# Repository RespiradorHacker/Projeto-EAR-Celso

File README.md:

# e-AR (EAR) PROJECT - EMERGENCY VENTILATOR
This project was born because of CoVid19 pandemic.
The project Goal is to provide an emergency ventilator system to help CoVid19 serious cases using locally available resources. eAR was designed to meet specifications according to MHRA (UK) - Rapidly Manufactured Ventilator System and inspired by MIT E-Vent (USA) concepts and specs.

This is an OPEN HARDWARE - OPEN SOURCE PROJECT. 

DISCLAIMER: we will NOT take any responsability on devices built using partial or total information from this project. 
Any device used for life support and medical applications must meet all local requirements and they must be homologated by local regulatory agencies in ANY case.

The target is to run an entire ventilation system using an automotive car battery and an O2 can.
The initial project leader is Celso Ken Mori Monteiro, automotive designer with +30 yrs experience on automotive embedded systems
as OEM designer for customers as GM, Ford, VW, Fiat, Mercedes Benz, Scania, Navistar, Marcopolo, Agco...

The technology for first PCBs was downsized due to components availability in emerging countries so distributed production could be achieved even in small brazilian towns. The electronic parts are:
- PTH components
- Single-sided PCB, obtainable even by DIYs. 

Besides inclusive concept there is also a FR4 SMT version available for volume production.

Basic concepts:
- External FIO2 O2 + AIR mixer based on timed mechanical truck air valves and plastic bag container
- AMBU smasher based on car window motor due to availabilty and great mechanical characteristics. Motor reversion is necessary to allow dinamic changes of BPM, Tidal Volume, pressure ramping, I/E Ratio and Plateau Hold Time without ANY mechanical change.
- ECU based on Arduino Pro Mini (the most available in emerging countries) and SPI based IO expension
- 2 motor drive options: relay (need second adjustable supply or buck) and PWM driven mosfet driver

Project Evolution:
- full HW schematics and system component's description available on "EAR System Developer's HW Guide", portuguese only version
- PCB Gerbers available, Single Side PTH version, Motor driver on relay option only. Time and size were underestimated because we no longer use these old technologies. Released on March 30, 2020.
- Mech prototype phase 2 aproved, torque is OK and current is low.
- Gerbers of single sided boards on PTH components published on March 30, 2020. Time and size were underestimated because we no longer use these old technologies. 
- EAR System Developer's SW Guide released on March 30, 2020.
- Functional electronics prototype built and delivered on April 2, 2020. No changes in PCBs are necessary except hardware end-of-courses provided for EAR ECU Motor Driver Board. Test driven by firmware FW00 - focused on HW testing only. Reads input pots, control motor with reversal action, measures motor current and tests IO expansion board. All items are functional.
- FW00 published in April 3, 2020.
- Added Mosfet-based PWM Motor Driver and Absolute position sensor using a car fuel level sensor.
- First working mechanical+electrical prototype delivered in April 6, 2020.
- Added Pressure Sensor in April 7, 2020. First artificial lung is a balloon so first pressure profile was obtained. It Sounds promising.
- Firmware controls Tidal Volume and BPM according to Set Potentiometers. First functional firmware produce variable pressure ramps as needed, FW met 8-30 BPM dynamic range specification.
- Added motor cutoff in inspiratory phase according to pressure preset on pot Overpressure Threshold within 1cm H20 resolution.
- Added full mechanical design for functional AMBU compressing ARM in April 11, 2020
- Added in April 12, 2020: Motor Driver, mosfet NN version. Full Kicad design with schematics, PCB and Gerbers.
- Added in April 12,2020: eAR External watchdog Timer to increase eAR reliability. Full Eagle design with schematics, PCB and Gerbers.
- Added in April 13,2020: I/E selection (1:1, 1:2, 1:3 and 1:4) and Plateau Hold Time selection (150, 250, 500 and 1000ms hold on Plateau)
- Added in April 13,2020: Gol G3 tank level float sensor added as absolute position sensor. Increased linearity, resolution and availability
- Mech proto 3.2 added ball bearing in compression arm, currently performing cycling tests
- Added in April 15,2020; eAR Pressure sensor Board Design and PCB, MPX5010DP supported
- Added in April 21,2020: 10x10cm FR4 SMT single PCB design for volume production, verified design, send to production
- Added in April 21,2020: Mechanical proto 3.2 drawings delivered, functional design
- April 30, 2004: eAR FR4 Single-Board PCBs arrived, courtesy from Digicart/SC
- May 1st, 2020: eAR system reached 14 days of 24/7 operation, with 403,412 beathing cycles completed. eAR met minimum durability MHRA (UK) Spec with a prototype built on MDF, a window lift BDC motor and a 20-yrs-old chevy tank float sensor
- May 5, 2020: Multiple pressure sensor added, allowing almost any kind of linear pressure sensor to be connected to eAR system, including MPX5010, MPX10 almost all versions and packages including MPVZ and MP3V and experimental ultra-low-cost MPS20N0040D-S sensor
- May 12, 2020: Integrated EAR ECU tested, functional test OK. Some minor drilling errors corrected, some improvements done and new PCB generated. New mosfet driver option added in firmware as needed. Some components changed values due to standardization effort to ease production. eAR electronics is ready for mass production.
- May 23, 2020: Added first steel based eAR mechanical design, by Ricardo Suzuki. Arm sensor changed to DS 1901 non-contact TPS. 
- June 1st, 2020: Added R2 of mechanical design in two verions, geared arm and 4-linked-bars by Ricardo Suzuki

Pending:
- Software reliability improvements.
- Assisted Ventilation Firmware on hold. It can delay ANVISA aproval when requested.

Special thanks to all people that made this project real!
It's impossible to list all names involved, I apologize for forgetting someone.
The partial list follows:

Project Contributors, as they have joined this project
- Joannes Berque (FR): first design idea.
- Celso Monteiro: eletronics and firmware design, system conception and documentation.
- Diego Padilha and Lucas Pianizzer: electronics and mechanical design+prototyping. 
- Marcelo Pires: electronic CAD, schematics capture & PCB Design.
- Nicolai Rutkevich: mechanical concepts.
- Bruno Afogliatto: decontamination concepts.
- Gustavo Ortenzi: motor drive alteratives.
- Ricardo Suzuki: system concepts and mechanical design.
- Rodrigo Azevedo: organized Github Project.
- Douglas Esteves: interface with other projects.
- João Cardoso and Leonardo Afonso: Kicad Capture for Open Hardware.
- Andre Novelli e Victor Acioly: AMBU bags replacement.
- Flavio Alves: GUI design
- David Loos: electronics assembly

References:
- MIT E-Vent: human requirements and system conception ideas.
- MHRA (UK) Rapidly Manufactured Ventilator System

Healthcare professionals involved:
- Angelica Mammana M.D. helped stablishing specs and performed crytical analysis.
- Fernando Machado M.D. was the first contributing doctor.
- Lucio Flavio M.D.
- Ana Teresa Gama.

Project supporters:
- Fabio Knihs.
- Norberto Tomio.
- Gabriel Casagrande.
- Ivandro Ceccato.

Thanks to my family, special thanks to my dear wife Tissa and my children Joana, Gustavo and Leonardo, for their unlimited support and to all the people that prayed for this project, and God that inspired and guided me all the time.

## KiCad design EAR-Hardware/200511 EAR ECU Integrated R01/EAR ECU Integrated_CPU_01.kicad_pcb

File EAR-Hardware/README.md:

# EAR ECU
Projeto iniciado por Celso Monteiro

- released RDSV200329 EAR System Developer's HW Guide PTBR R00
- This document has details on EAR ECU hardware and its components
- OPEN HARDWARE

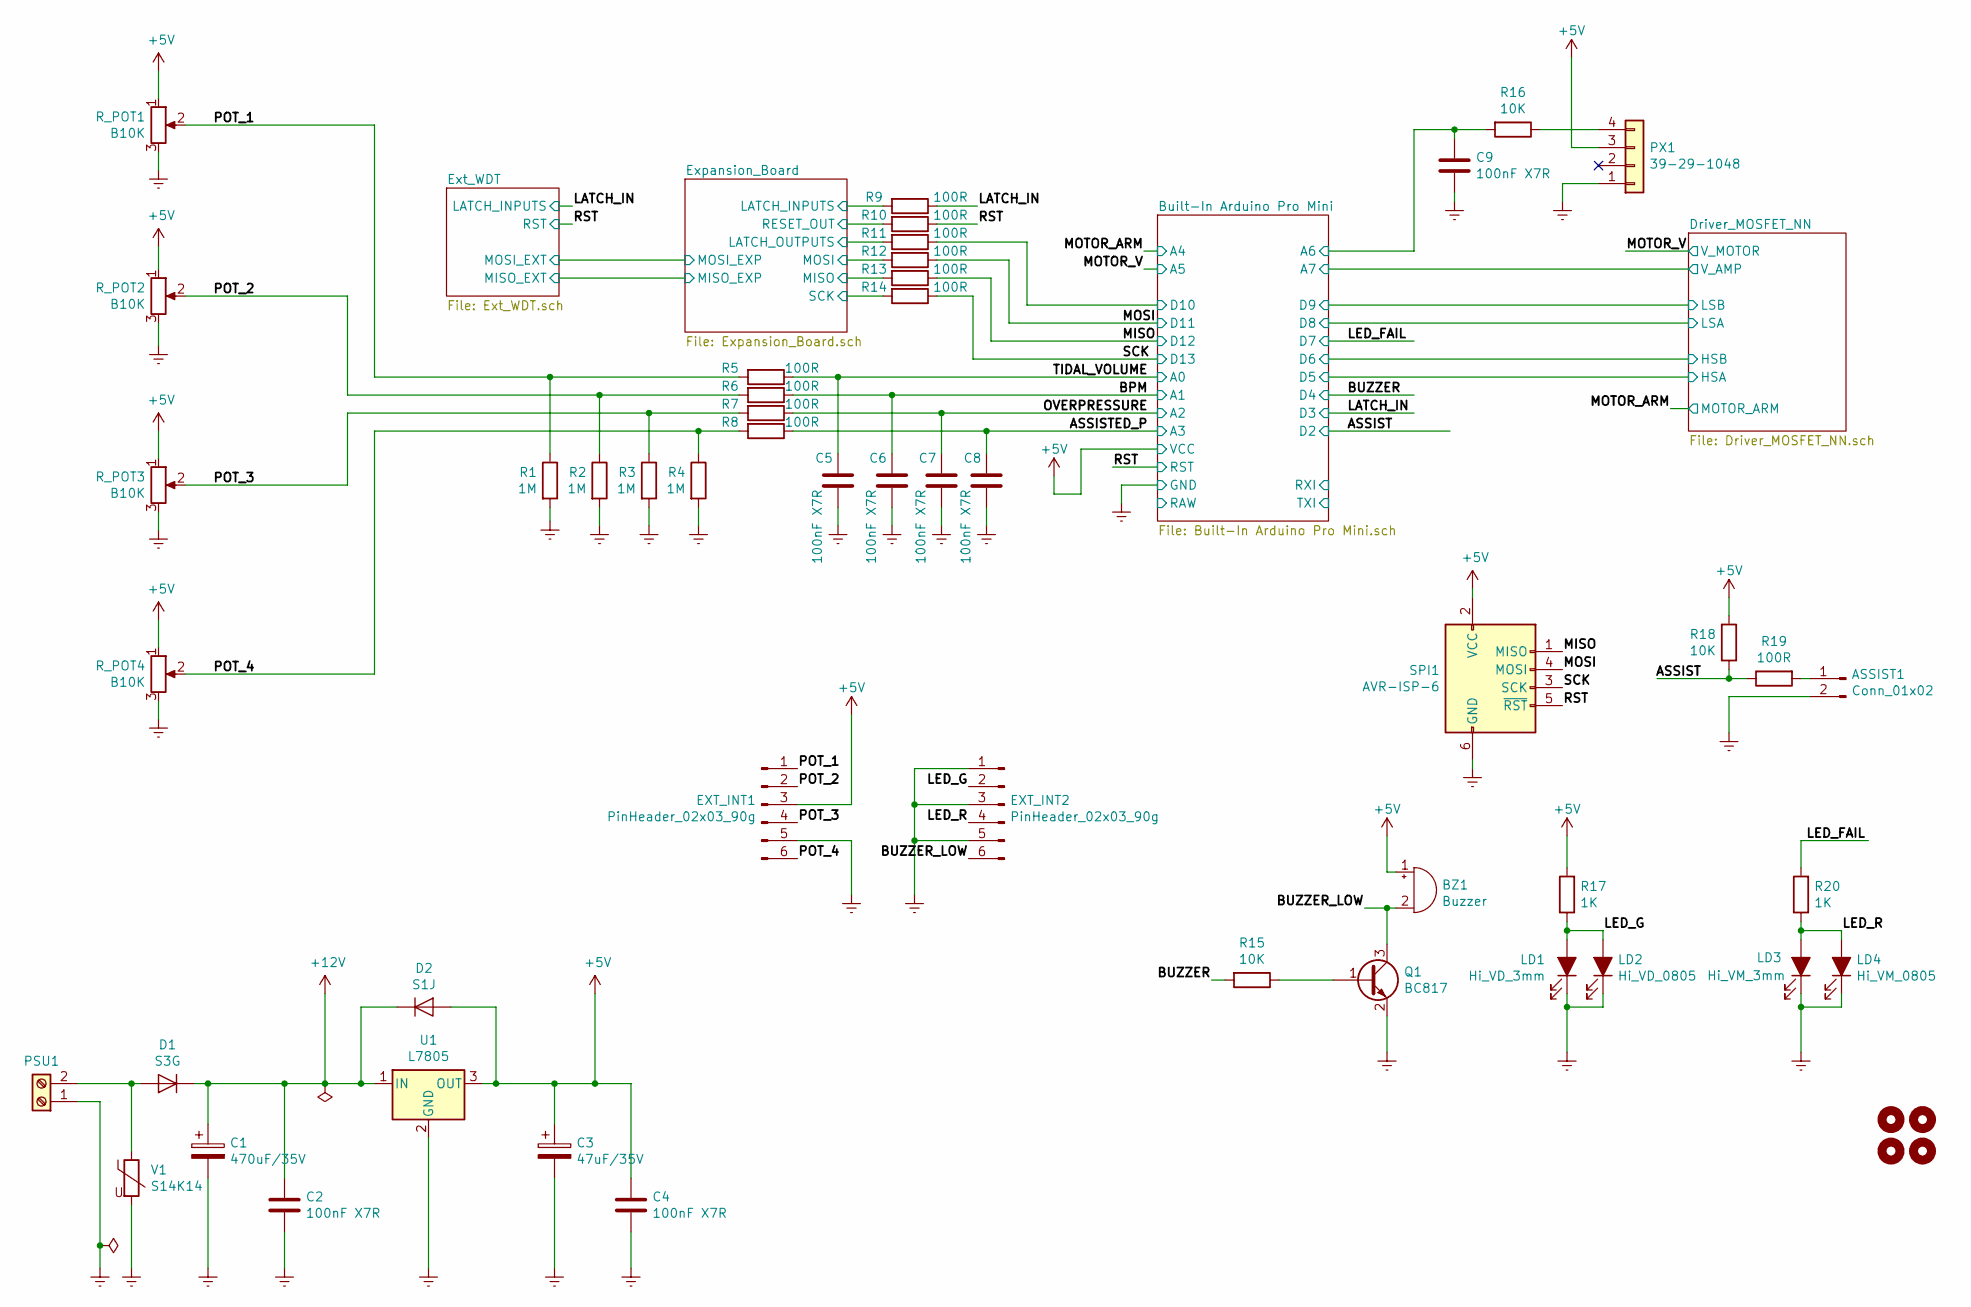
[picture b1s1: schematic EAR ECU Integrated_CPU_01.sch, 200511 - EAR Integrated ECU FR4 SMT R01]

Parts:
ASSIST1: Conn_01x02; SolderWirePad_1x02_P3.81mm_Drill1mm
BZ1: Buzzer; Buzzer_TDK_PS1240P02BT_D12.2mm_H6.5mm
C1: 470uF/35V; CP_Radial_D10.0mm_P5.00mm
C2, C4, C5, C6, C7, C8, C9: 100nF X7R; C_0805_2012Metric
C3: 47uF/35V; CP_Radial_D5.0mm_P2.50mm
D1: S3G; D_SMC
D2: S1J; D_SMA
EXT_INT1, EXT_INT2: PinHeader_02x03_90g; PinHeader_2x03_P2.54mm_Horizontal
H1, H2, H3, H4: MountingHole; MountingHole_3.5mm_Pad_Via
LD1: Hi_VD_3mm; LED_D3.0mm_Clear
LD2: Hi_VD_0805; LED_0805_2012Metric
LD3: Hi_VM_3mm; LED_D3.0mm_Clear
LD4: Hi_VM_0805; LED_0805_2012Metric
PSU1: TerminalBlock_Phoenix:TerminalBlock_Phoenix_MKDS-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; TerminalBlock_Phoenix_MKDS-1,5-2-5.08_1x02_P5.08mm_Horizont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
PX1: 39-29-1048; MOLEX-39-29-1048
Q1: BC817; SOT-23
R1, R2, R3, R4: 1M; R_0805_2012Metric
R5, R6, R7, R8, R9, R10, R11, R12, R13, R14, R19: 100R; R_0805_2012Metric
R15, R16, R18: 10K; R_0805_2012Metric
R17, R20: 1K; R_0805_2012Metric
R_POT1, R_POT2, R_POT3, R_POT4: B10K; PDB18_Series_Bourns
SPI1: AVR-ISP-6; PinHeader_2x03_P2.54mm_Vertical
U1: L7805; TO-263-3_Hybrid_TO-220_Tab_Dw
V1: S14K14; RV_Disc_D12mm_W3.9mm_P7.5mm

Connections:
+5V: BZ1.1 (-), C3.1, C4.1, D2.2 (A), EXT_INT1.3, PX1.3, R17.2, R18.2, R_POT1.1, R_POT2.1, R_POT3.1, R_POT4.1, SPI1.2 (VCC), U1.3 (OUT); also elsewhere on the board
+12V: C1.1, C2.1, D1.1 (K), D2.1 (K), U1.1 (IN); also elsewhere on the board
/ASSIST: R18.1, R19.1; also elsewhere on the board
/ASSISTED_P: C8.1, R8.1; also elsewhere on the board
/BPM: C6.1, R6.1; also elsewhere on the board
/BUZZER: R15.2; also elsewhere on the board
/BUZZER_LOW: BZ1.2 (+), EXT_INT2.6, Q1.3 (C)
/Built-In Arduino Pro Mini/A6: C9.1, R16.2; also elsewhere on the board
/Built-In Arduino Pro Mini/D10: R11.1; also elsewhere on the board
/Expansion_Board/LATCH_INPUTS: R9.2; also elsewhere on the board
/Expansion_Board/LATCH_OUTPUTS: R11.2; also elsewhere on the board
/Expansion_Board/MISO: R13.2; also elsewhere on the board
/Expansion_Board/MOSI: R12.2; also elsewhere on the board
/Expansion_Board/RESET_OUT: R10.2; also elsewhere on the board
/Expansion_Board/SCK: R14.2; also elsewhere on the board
/LATCH_IN: R9.1; also elsewhere on the board
/LED_FAIL: R20.2; also elsewhere on the board
/LED_G: EXT_INT2.2, LD1.2 (A), LD2.2 (A), R17.1
/LED_R: EXT_INT2.4, LD3.2 (A), LD4.2 (A), R20.1
/MISO: R13.1, SPI1.1 (MISO); also elsewhere on the board
/MOSI: R12.1, SPI1.4 (MOSI); also elsewhere on the board
/OVERPRESSURE: C7.1, R7.1; also elsewhere on the board
/POT_1: EXT_INT1.1, R1.1, R5.2, R_POT1.2
/POT_2: EXT_INT1.2, R2.1, R6.2, R_POT2.2
/POT_3: EXT_INT1.4, R3.1, R7.2, R_POT3.2
/POT_4: EXT_INT1.6, R4.1, R8.2, R_POT4.2
/RST: R10.1, SPI1.5 (~RST); also elsewhere on the board
/SCK: R14.1, SPI1.3 (SCK); also elsewhere on the board
/TIDAL_VOLUME: C5.1, R5.1; also elsewhere on the board
unnamed: ASSIST1.1, R19.2
unnamed: D1.2 (A), PSU1.2, V1.1
unnamed: PX1.4, R16.1
unnamed: Q1.1 (B), R15.1

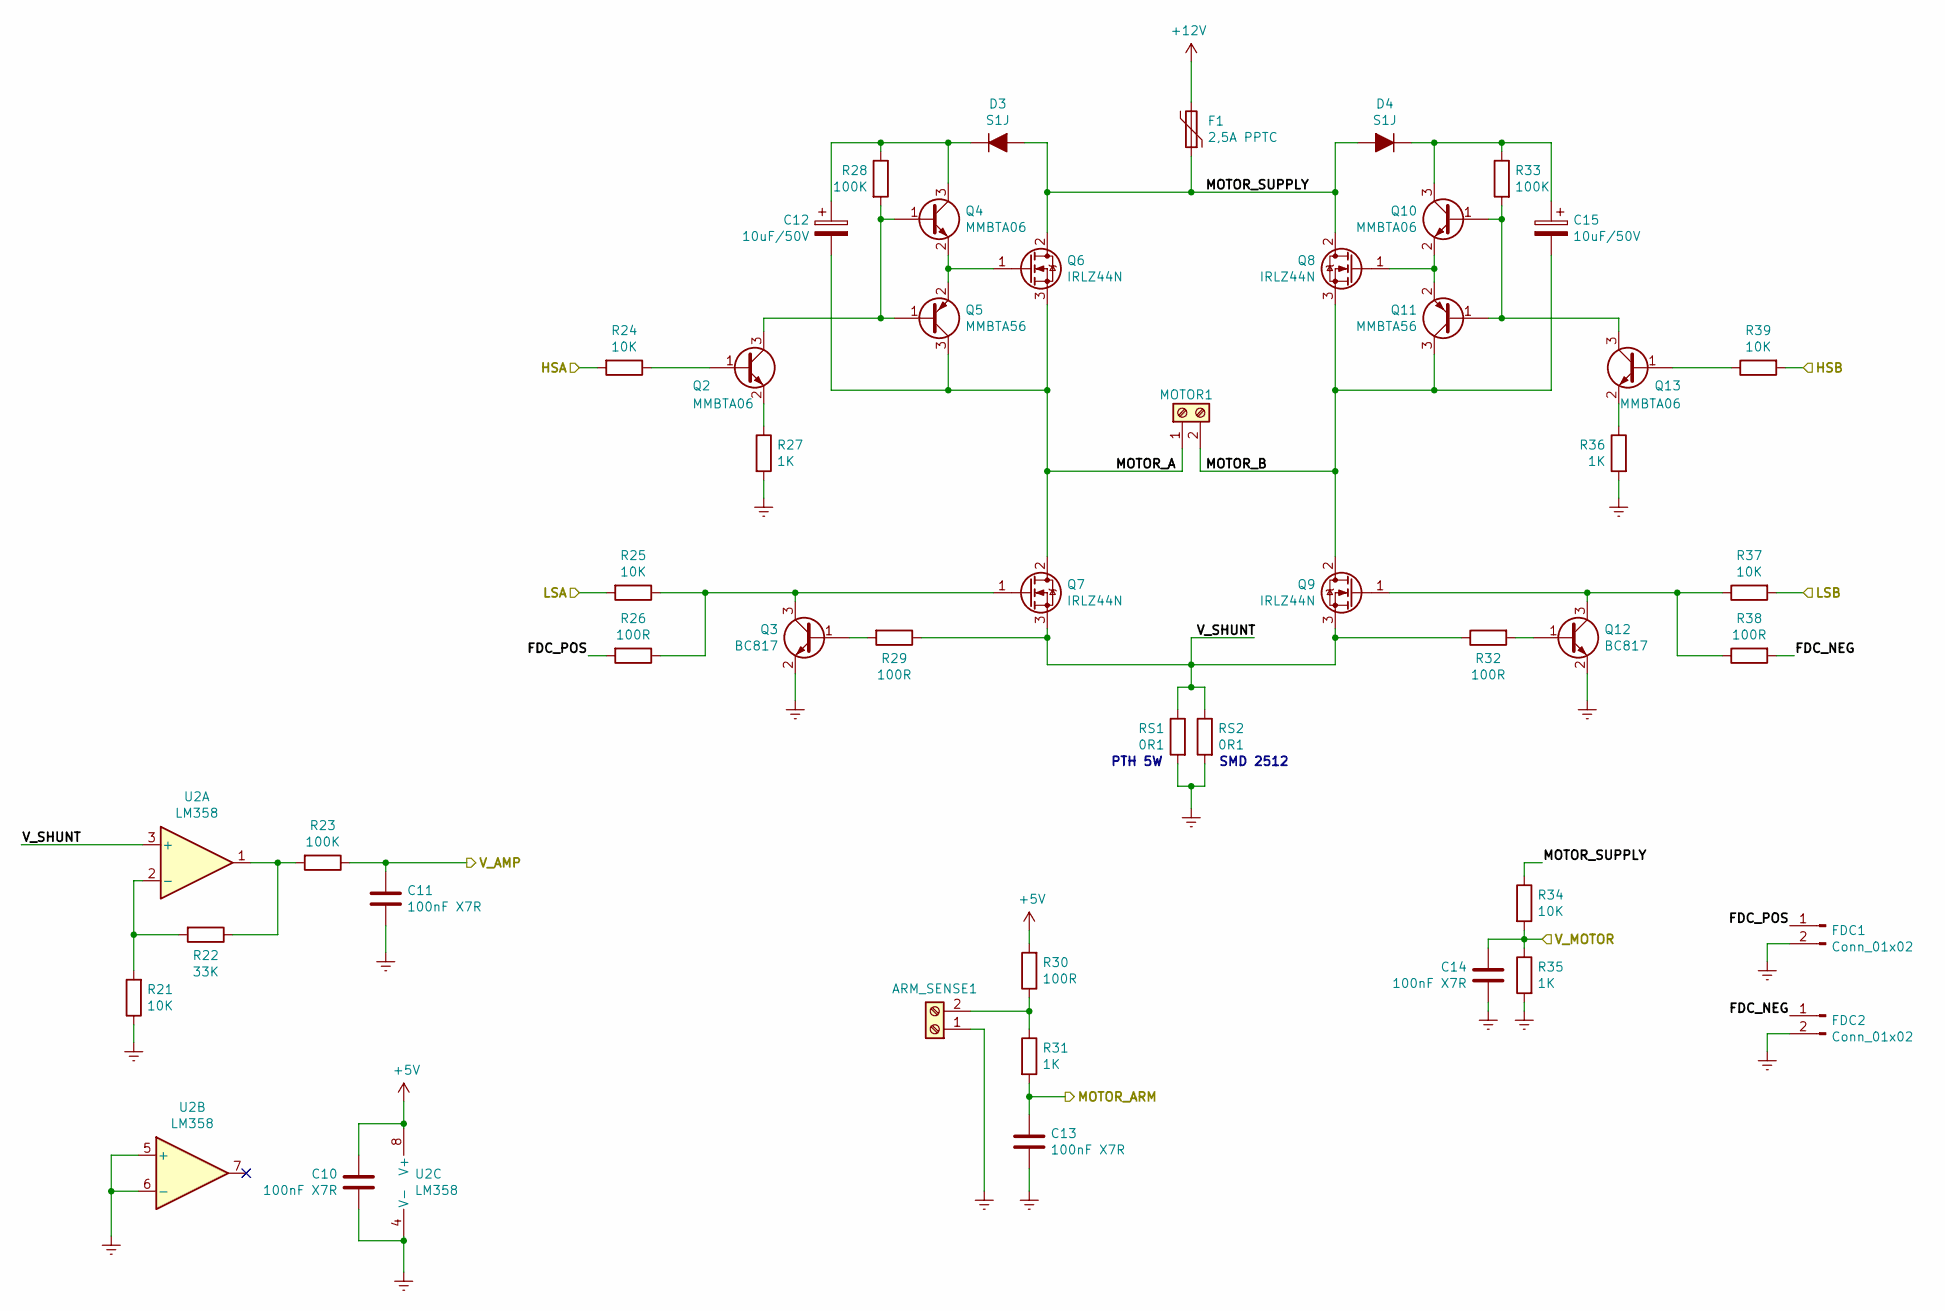
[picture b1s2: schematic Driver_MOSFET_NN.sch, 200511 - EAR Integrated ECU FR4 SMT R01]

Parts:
ARM_SENSE1: Screw_Terminal_01x02; TerminalBlock_Phoenix_MKDS-1,5-2-5.08_1x02_P5.08mm_Horizont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
C10, C11, C13, C14: 100nF X7R; C_0805_2012Metric
C12, C15: 10uF/50V; CP_Radial_D5.0mm_P2.50mm
D3, D4: S1J; D_SMA
F1: 2,5A PPTC; RV_Disc_D7mm_W3.4mm_P5mm
FDC1, FDC2: Conn_01x02; PinSocket_1x02_P2.54mm_Vertical
MOTOR1: Conn_01x02; TerminalBlock_Phoenix_MKDS-1,5-2-5.08_1x02_P5.08mm_Horizont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
Q2, Q4, Q10, Q13: MMBTA06; SOT-23
Q3, Q12: BC817; SOT-23
Q5, Q11: MMBTA56; SOT-23
Q6, Q7, Q8, Q9: IRLZ44N; TO-263-3_Hybrid_TO-220_Tab_Dw
R21, R24, R25, R34, R37, R39: 10K; R_0805_2012Metric
R22: 33K; R_0805_2012Metric
R23, R28, R33: 100K; R_0805_2012Metric
R26, R29, R30, R32, R38: 100R; R_0805_2012Metric
R27, R31, R35, R36: 1K; R_0805_2012Metric
RS1: 0R1; R_Axial_Power_L20.0mm_W6.4mm_P7.62mm_Vertical
RS2: 0R1; R_2512_6332Metric_Pad1.52x3.35mm_HandSolder
U2: LM358; SOIC-8_3.9x4.9mm_P1.27mm

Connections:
+5V: C10.1, R30.2, U2.8 (V+); also elsewhere on the board
+12V: F1.2; also elsewhere on the board
/Built-In Arduino Pro Mini/A7: C11.1, R23.1; also elsewhere on the board
/Built-In Arduino Pro Mini/D5: R24.2; also elsewhere on the board
/Built-In Arduino Pro Mini/D6: R39.2; also elsewhere on the board
/Built-In Arduino Pro Mini/D8: R25.2; also elsewhere on the board
/Built-In Arduino Pro Mini/D9: R37.2; also elsewhere on the board
/Driver_MOSFET_NN/FDC_NEG: FDC2.1, R38.2
/Driver_MOSFET_NN/FDC_POS: FDC1.1, R26.2
/Driver_MOSFET_NN/MOTOR_A: C12.2, MOTOR1.1, Q5.3 (C), Q6.3 (S), Q7.2 (D)
/Driver_MOSFET_NN/MOTOR_B: C15.2, MOTOR1.2, Q8.3 (S), Q9.2 (D), Q11.3 (C)
/Driver_MOSFET_NN/MOTOR_SUPPLY: D3.2 (A), D4.2 (A), F1.1, Q6.2 (D), Q8.2 (D), R34.1
/Driver_MOSFET_NN/Q6G: Q4.2 (E), Q5.2 (E), Q6.1 (G)
/Driver_MOSFET_NN/Q7G: Q3.3 (C), Q7.1 (G), R25.1, R26.1
/Driver_MOSFET_NN/Q8G: Q8.1 (G), Q10.2 (E), Q11.2 (E)
/Driver_MOSFET_NN/Q9G: Q9.1 (G), Q12.3 (C), R37.1, R38.1
/Driver_MOSFET_NN/V_SHUNT: Q7.3 (S), Q9.3 (S), R29.1, R32.1, RS1.1, RS2.1, U2.3 (+)
/MOTOR_ARM: C13.1, R31.2; also elsewhere on the board
/MOTOR_V: C14.1, R34.2, R35.1; also elsewhere on the board
unnamed: ARM_SENSE1.2, R30.1, R31.1
unnamed: C12.1, D3.1 (K), Q4.3 (C), R28.1
unnamed: C15.1, D4.1 (K), Q10.3 (C), R33.1
unnamed: Q2.1 (B), R24.1
unnamed: Q2.2 (E), R27.1
unnamed: Q2.3 (C), Q4.1 (B), Q5.1 (B), R28.2
unnamed: Q3.1 (B), R29.2
unnamed: Q10.1 (B), Q11.1 (B), Q13.3 (C), R33.2
unnamed: Q12.1 (B), R32.2
unnamed: Q13.1 (B), R39.1
unnamed: Q13.2 (E), R36.1
unnamed: R21.2, R22.2, U2.2 (-)
unnamed: R22.1, R23.2, U2.1

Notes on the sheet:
PTH 5W
SMD 2512

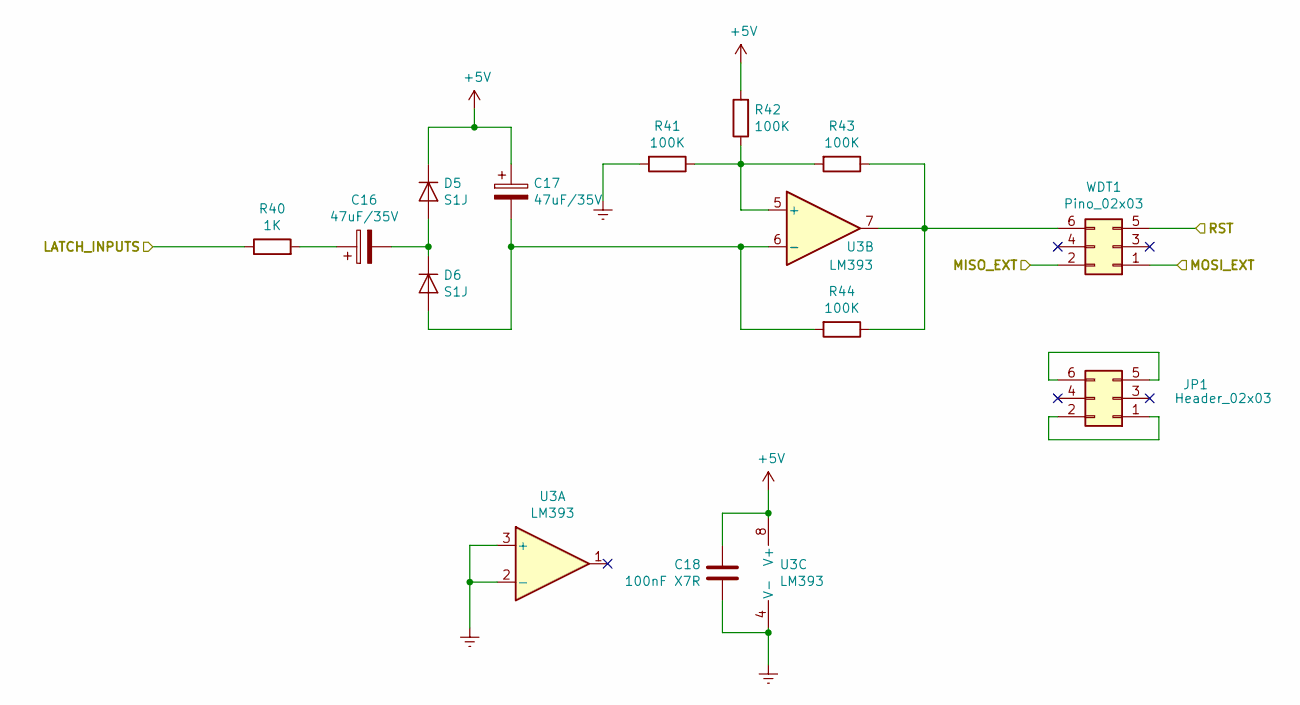
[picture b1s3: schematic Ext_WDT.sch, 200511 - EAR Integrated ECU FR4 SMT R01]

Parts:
C16, C17: 47uF/35V; CP_Radial_D5.0mm_P2.50mm
C18: 100nF X7R; C_0805_2012Metric
D5, D6: S1J; D_SMA
JP1: Header_02x03; PinSocket_2x03_P2.54mm_Vertical
R40: 1K; R_0805_2012Metric
R41, R42, R43, R44: 100K; R_0805_2012Metric
U3: LM393; SOIC-8_3.9x4.9mm_P1.27mm
WDT1: Pino_02x03; PinHeader_2x03_P2.54mm_Vertical

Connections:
+5V: C17.1, C18.1, D5.1 (K), R42.2, U3.8 (V+); also elsewhere on the board
/Expansion_Board/MISO_EXP: WDT1.2; also elsewhere on the board
/Expansion_Board/MOSI_EXP: WDT1.1; also elsewhere on the board
/LATCH_IN: R40.1; also elsewhere on the board
/RST: WDT1.5; also elsewhere on the board
unnamed: C16.1, R40.2
unnamed: C16.2, D5.2 (A), D6.1 (K)
unnamed: C17.2, D6.2 (A), R44.2, U3.6 (-)
unnamed: JP1.1, JP1.2
unnamed: JP1.5, JP1.6
unnamed: R41.1, R42.1, R43.2, U3.5 (+)
unnamed: R43.1, R44.1, U3.7, WDT1.6

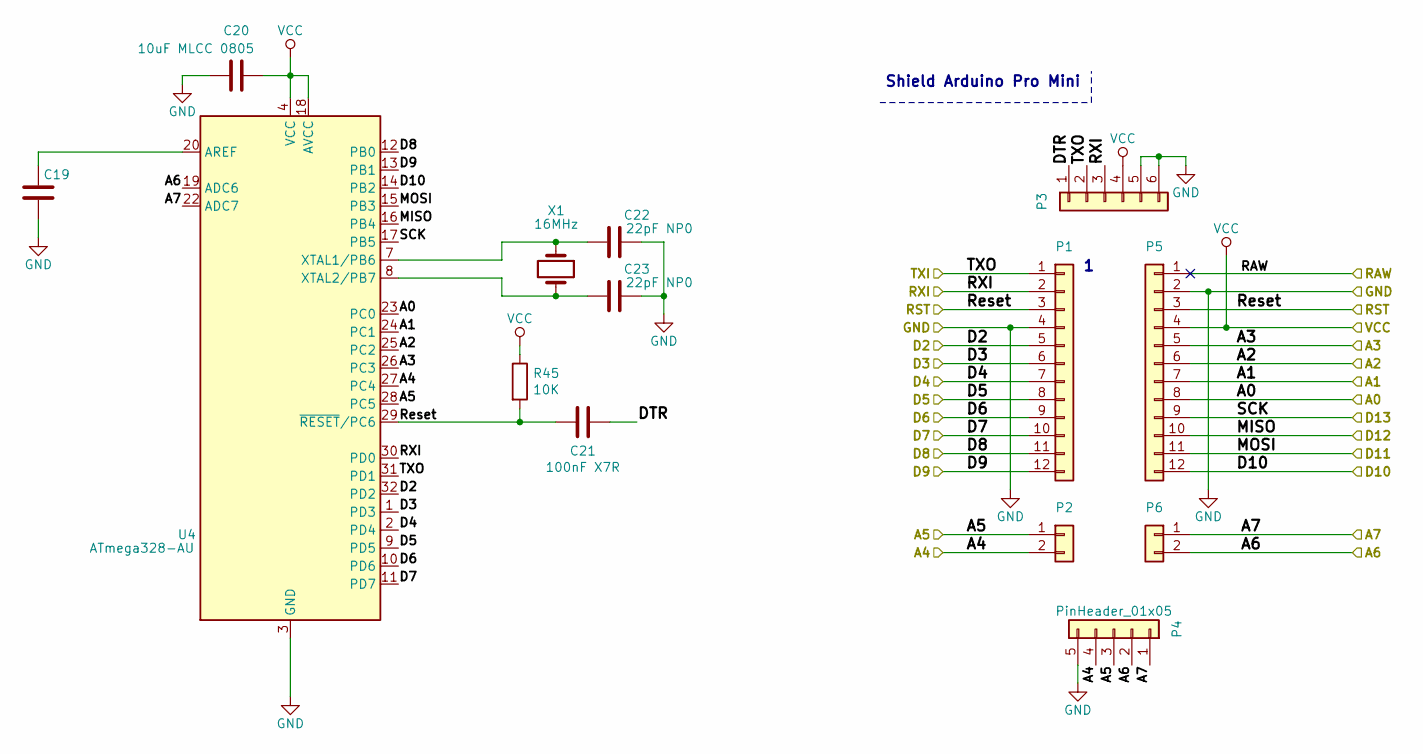
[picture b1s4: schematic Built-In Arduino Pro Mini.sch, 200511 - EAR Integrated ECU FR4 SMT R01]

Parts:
C19, C21: 100nF X7R; C_0805_2012Metric
C20: 10uF MLCC 0805; C_0805_2012Metric
C22, C23: 22pF NP0; C_0805_2012Metric
P1, P5: PinHeader_01x12; PinHeader_1x12_P2.54mm_Vertical
P2, P6: PinHeader_01x02; PinHeader_1x02_P2.54mm_Vertical
P3: PinHeader_01x06; PinHeader_1x06_P2.54mm_Vertical
P4: PinHeader_01x05; PinHeader_1x05_P2.54mm_Vertical
R45: 10K; R_0805_2012Metric
U4: ATmega328-AU; TQFP-32_7x7mm_P0.8mm
X1: 16MHz; Crystal_HC49-4H_Vertical

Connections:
+5V: C20.2, P3.4, P5.4, R45.1, U4.4 (VCC), U4.6 (VCC), U4.18 (AVCC); also elsewhere on the board
/ASSIST: P1.5, U4.32 (PD2); also elsewhere on the board
/ASSISTED_P: P5.5, U4.26 (PC3); also elsewhere on the board
/BPM: P5.7, U4.24 (PC1); also elsewhere on the board
/BUZZER: P1.7, U4.2 (PD4); also elsewhere on the board
/Built-In Arduino Pro Mini/A6: P4.2, P6.2, U4.19 (ADC6); also elsewhere on the board
/Built-In Arduino Pro Mini/A7: P4.1, P6.1, U4.22 (ADC7); also elsewhere on the board
/Built-In Arduino Pro Mini/D5: P1.8, U4.9 (PD5); also elsewhere on the board
/Built-In Arduino Pro Mini/D6: P1.9, U4.10 (PD6); also elsewhere on the board
/Built-In Arduino Pro Mini/D8: P1.11, U4.12 (PB0); also elsewhere on the board
/Built-In Arduino Pro Mini/D9: P1.12, U4.13 (PB1); also elsewhere on the board
/Built-In Arduino Pro Mini/D10: P5.12, U4.14 (PB2); also elsewhere on the board
/Built-In Arduino Pro Mini/DTR: C21.2, P3.1
/Built-In Arduino Pro Mini/RAW: P5.1
/Built-In Arduino Pro Mini/RXI: P1.2, P3.3, U4.30 (PD0)
/Built-In Arduino Pro Mini/TXI: P1.1, P3.2, U4.31 (PD1)
/LATCH_IN: P1.6, U4.1 (PD3); also elsewhere on the board
/LED_FAIL: P1.10, U4.11 (PD7); also elsewhere on the board
/MISO: P5.10, U4.16 (PB4); also elsewhere on the board
/MOSI: P5.11, U4.15 (PB3); also elsewhere on the board
/MOTOR_ARM: P2.2, P4.4, U4.27 (PC4); also elsewhere on the board
/MOTOR_V: P2.1, P4.3, U4.28 (PC5); also elsewhere on the board
/OVERPRESSURE: P5.6, U4.25 (PC2); also elsewhere on the board
/RST: C21.1, P1.3, P5.3, R45.2, U4.29 (~RESET~/PC6); also elsewhere on the board
/SCK: P5.9, U4.17 (PB5); also elsewhere on the board
/TIDAL_VOLUME: P5.8, U4.23 (PC0); also elsewhere on the board
unnamed: C19.1, U4.20 (AREF)
unnamed: C22.1, U4.7 (XTAL1/PB6), X1.1
unnamed: C23.1, U4.8 (XTAL2/PB7), X1.2

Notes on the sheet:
Shield Arduino Pro Mini

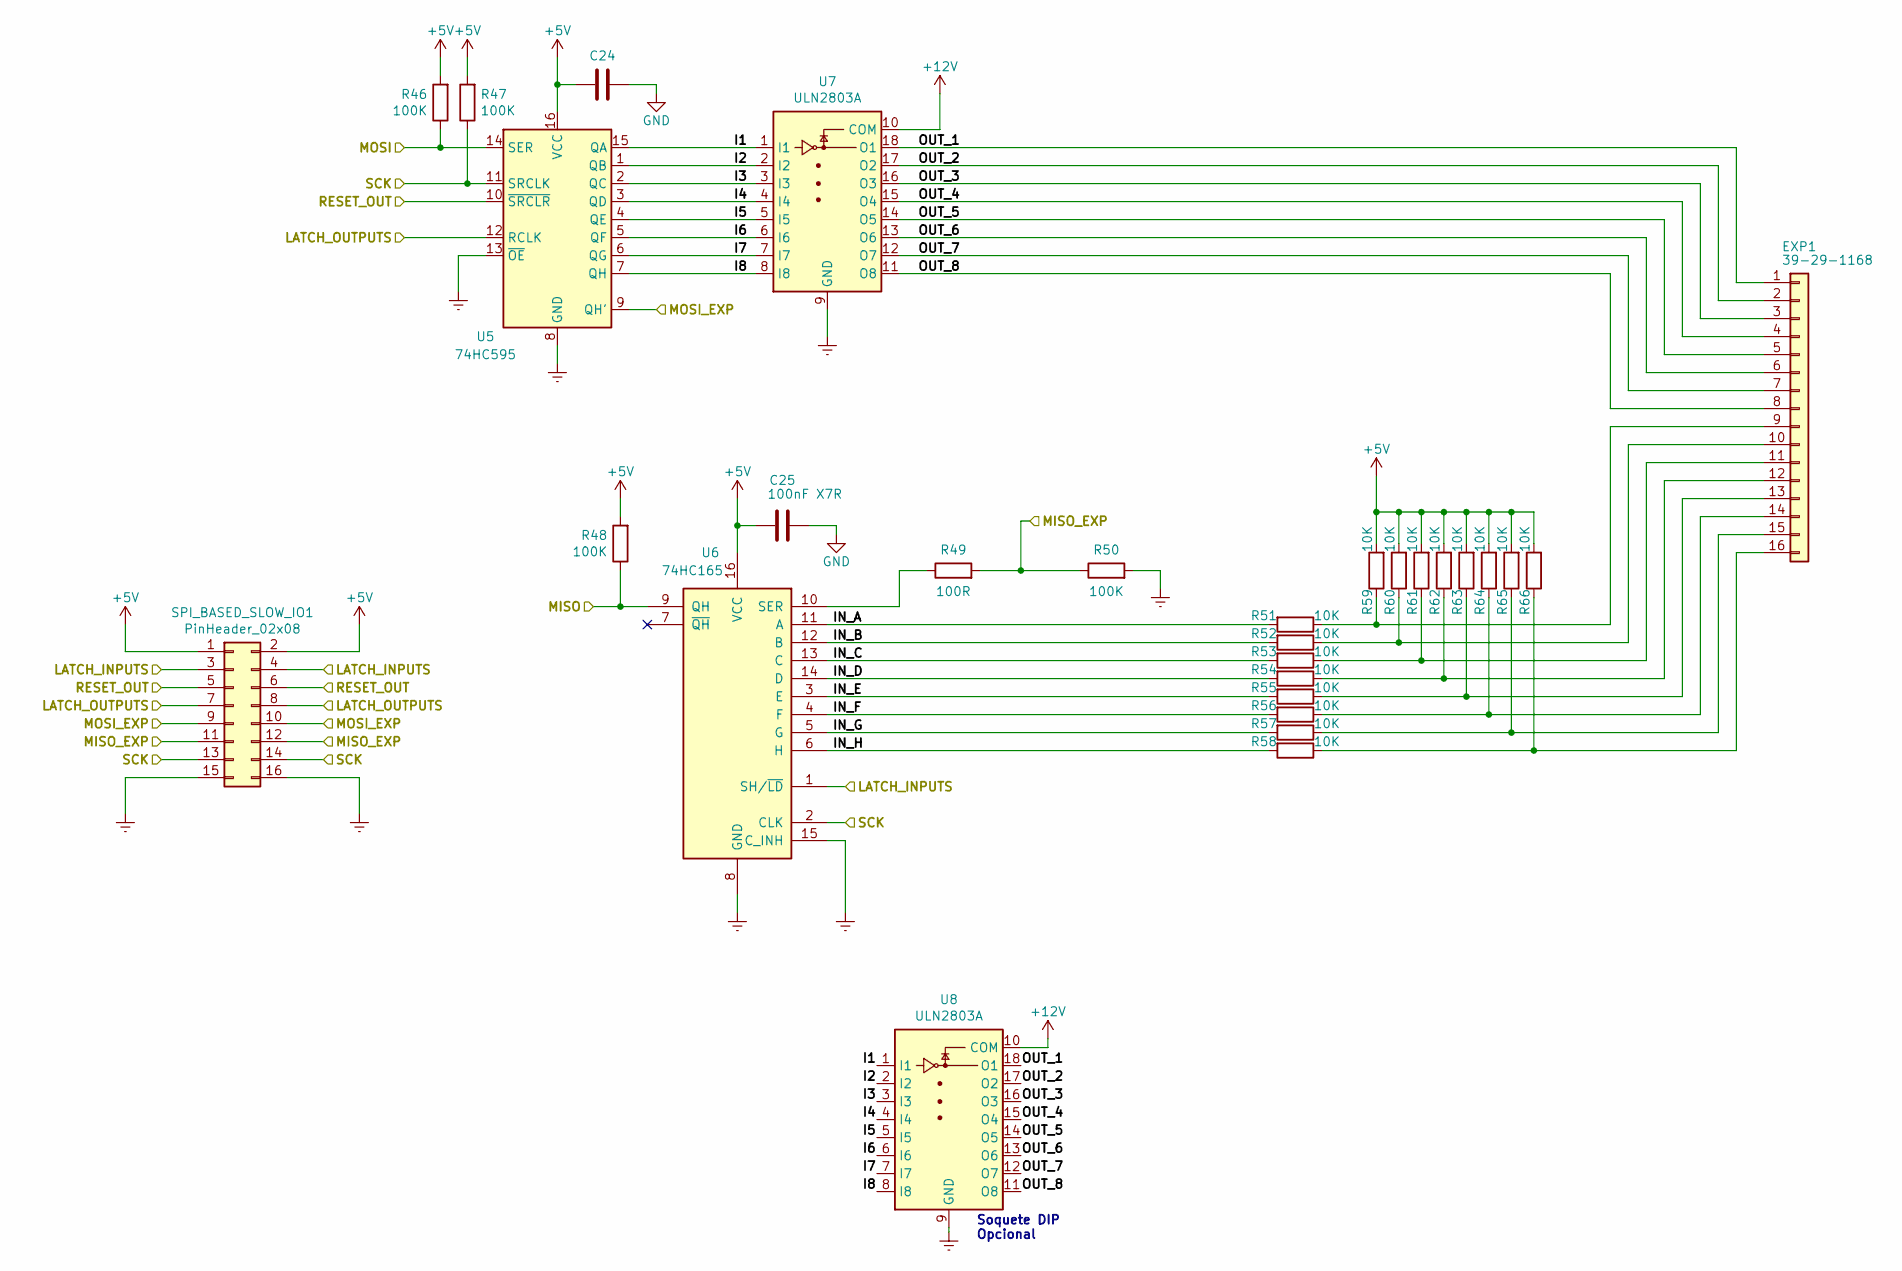
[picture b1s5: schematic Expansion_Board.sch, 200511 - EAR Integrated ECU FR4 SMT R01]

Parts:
C24, C25: 100nF X7R; C_0805_2012Metric
EXP1: 39-29-1168; MOLEX-39-29-1168
R46, R47, R48, R50: 100K; R_0805_2012Metric
R49: 100R; R_0805_2012Metric
R51, R52, R53, R54, R55, R56, R57, R58, R59, R60, R61, R62, R63, R64, R65, R66: 10K; R_0805_2012Metric
SPI_BASED_SLOW_IO1: PinHeader_02x08; PinHeader_2x08_P2.54mm_Vertical
U5: 74HC595; SOIC-16_3.9x9.9mm_P1.27mm
U6: 74HC165; SOIC-16_3.9x9.9mm_P1.27mm
U7: ULN2803A; SOIC-18W_7.5x11.6mm_P1.27mm
U8: ULN2803A; DIP-18_W7.62mm

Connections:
+5V: C24.2, C25.2, R46.2, R47.2, R48.2, R59.2, R60.2, R61.2, R62.2, R63.2, R64.2, R65.2, R66.2, SPI_BASED_SLOW_IO1.1, SPI_BASED_SLOW_IO1.2, U5.16 (VCC), U6.16 (VCC); also elsewhere on the board
+12V: U7.10 (COM), U8.10 (COM); also elsewhere on the board
/Expansion_Board/I1: U5.15 (QA), U7.1 (I1), U8.1 (I1)
/Expansion_Board/I2: U5.1 (QB), U7.2 (I2), U8.2 (I2)
/Expansion_Board/I3: U5.2 (QC), U7.3 (I3), U8.3 (I3)
/Expansion_Board/I4: U5.3 (QD), U7.4 (I4), U8.4 (I4)
/Expansion_Board/I5: U5.4 (QE), U7.5 (I5), U8.5 (I5)
/Expansion_Board/I6: U5.5 (QF), U7.6 (I6), U8.6 (I6)
/Expansion_Board/I7: U5.6 (QG), U7.7 (I7), U8.7 (I7)
/Expansion_Board/I8: U5.7 (QH), U7.8 (I8), U8.8 (I8)
/Expansion_Board/IN_A: R51.2, U6.11 (A)
/Expansion_Board/IN_B: R52.2, U6.12 (B)
/Expansion_Board/IN_C: R53.2, U6.13 (C)
/Expansion_Board/IN_D: R54.2, U6.14 (D)
/Expansion_Board/IN_E: R55.2, U6.3 (E)
/Expansion_Board/IN_F: R56.2, U6.4 (F)
/Expansion_Board/IN_G: R57.2, U6.5 (G)
/Expansion_Board/IN_H: R58.2, U6.6 (H)
/Expansion_Board/LATCH_INPUTS: SPI_BASED_SLOW_IO1.3, SPI_BASED_SLOW_IO1.4, U6.1 (SH/~LD); also elsewhere on the board
/Expansion_Board/LATCH_OUTPUTS: SPI_BASED_SLOW_IO1.7, SPI_BASED_SLOW_IO1.8, U5.12 (RCLK); also elsewhere on the board
/Expansion_Board/MISO: R48.1, U6.9 (QH); also elsewhere on the board
/Expansion_Board/MISO_EXP: R49.2, R50.1, SPI_BASED_SLOW_IO1.11, SPI_BASED_SLOW_IO1.12; also elsewhere on the board
/Expansion_Board/MOSI: R46.1, U5.14 (SER); also elsewhere on the board
/Expansion_Board/MOSI_EXP: SPI_BASED_SLOW_IO1.9, SPI_BASED_SLOW_IO1.10, U5.9 (QH'); also elsewhere on the board
/Expansion_Board/OUT_1: EXP1.1, U7.18 (O1), U8.18 (O1)
/Expansion_Board/OUT_2: EXP1.2, U7.17 (O2), U8.17 (O2)
/Expansion_Board/OUT_3: EXP1.3, U7.16 (O3), U8.16 (O3)
/Expansion_Board/OUT_4: EXP1.4, U7.15 (O4), U8.15 (O4)
/Expansion_Board/OUT_5: EXP1.5, U7.14 (O5), U8.14 (O5)
/Expansion_Board/OUT_6: EXP1.6, U7.13 (O6), U8.13 (O6)
/Expansion_Board/OUT_7: EXP1.7, U7.12 (O7), U8.12 (O7)
/Expansion_Board/OUT_8: EXP1.8, U7.11 (O8), U8.11 (O8)
/Expansion_Board/RESET_OUT: SPI_BASED_SLOW_IO1.5, SPI_BASED_SLOW_IO1.6, U5.10 (~SRCLR); also elsewhere on the board
/Expansion_Board/SCK: R47.1, SPI_BASED_SLOW_IO1.13, SPI_BASED_SLOW_IO1.14, U5.11 (SRCLK), U6.2 (CLK); also elsewhere on the board
unnamed: EXP1.9, R51.1, R59.1
unnamed: EXP1.10, R52.1, R60.1
unnamed: EXP1.11, R53.1, R61.1
unnamed: EXP1.12, R54.1, R62.1
unnamed: EXP1.13, R55.1, R63.1
unnamed: EXP1.14, R56.1, R64.1
unnamed: EXP1.15, R57.1, R65.1
unnamed: EXP1.16, R58.1, R66.1
unnamed: R49.1, U6.10 (SER)

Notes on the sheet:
Soquete DIP Opcional

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
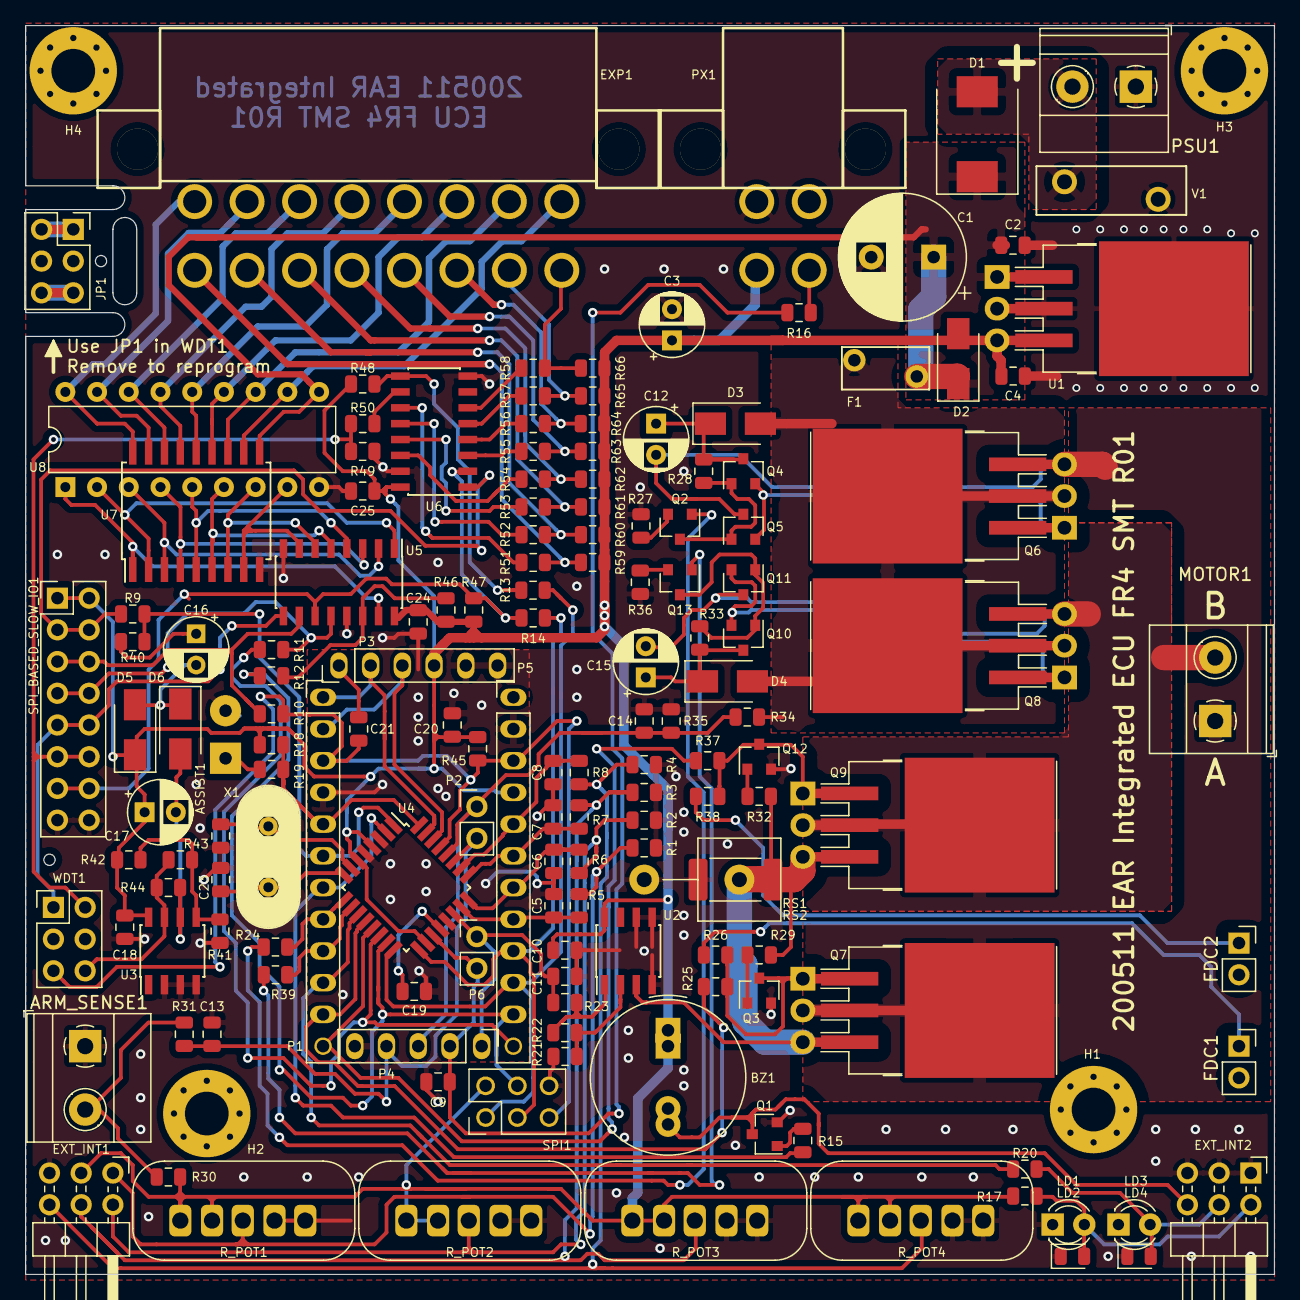
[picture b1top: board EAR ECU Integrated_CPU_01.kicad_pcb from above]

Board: 2 copper layers, 100.0 x 100.0 mm, 156 parts (0 on the bottom side), 112 nets.

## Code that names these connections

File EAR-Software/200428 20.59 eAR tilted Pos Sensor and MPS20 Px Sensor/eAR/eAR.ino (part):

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 - TR is from 51 to 235 (30-8 BPM) assuming 150ms of Plateau_Hold_Time
 - Ramping_Speed=(TidalVolumeSet*8)/Ramping_Insp_Time; 
    - 8 is a mult constant used to increase resolution
 - Ramping_Speed values ranged from 6 (8 BPM - 200 ml TV) to 125 (30 BPM - 800 ml TV)
 
#R200409EAR03 - Calculates PWM based on Ramping_Speed  

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  #define Task_Common TRUE  //
#endif

#define Beep_On_OverPx TRUE // #R200410EAR01 - Enables Beep on overpressure

//#define SPI_Loopback_Mode 1 // SPI Loopback Mode is set for IO Expansion Testing - 

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//  END of Arm Position Sensor Definition
// =======================================

#define BPM_Min 8   // #R200408EAR05 - Implements BPM as f(pot)
#define BPM_Max 30  // #R200408EAR05 - Implements BPM as f(pot)

#define TVS_Min 200 // #R200408EAR07 - Implements TidalVolumeSet as f(pot)
#define TVS_Max 800 // #R200408EAR07 - Implements TidalVolumeSet as f(pot)
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  // #define sDump_PM TRUE   // Pressure Max Limit SET
  // #define sDump_AP TRUE   // Assisted Pressure Threshold SET
  #define sDump_TS TRUE   // Tidal Volume SET
  #define sDump_BM TRUE   // BPM SET
  #define sDump_IE TRUE   // IE SET
  #define sDump_PH TRUE   // Plateau Hold Time SET
  // #define sDump_TB TRUE   // Total BPM Time
  // #define sDump_TI TRUE   // Total Inspiration Time
  // #define sDump_TE TRUE   // Total Expiration Time
  // #define sDump_TR TRUE   // Ramping Inspiration Time
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  #define sDump_PM TRUE   // Pressure Max Limit SET
  #define sDump_AP TRUE   // Assisted Pressure Threshold SET
  #define sDump_TS TRUE   // Tidal Volume SET
  #define sDump_BM TRUE   // BPM SET
  #define sDump_IE TRUE   // IE SET
  #define sDump_PH TRUE   // Plateau Hold Time SET
  // #define sDump_TB TRUE   // Total BPM Time
  // #define sDump_TI TRUE   // Total Inspiration Time
  // #define sDump_TE TRUE   // Total Expiration Time
  // #define sDump_TR TRUE   // Ramping Inspiration Time
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// ===================================

#define BEEP 4           // BIP
#define Latch_Inputs 3   // IO baseado em SPI
#define Latch_Outputs 10 // IO baseado em SPI

#define LSA 8            // Low Side A Bridge !
#define LSB 9            // Low Side B Bridge !
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  pinMode(LSA, OUTPUT);
  pinMode(LSB, OUTPUT);
  pinMode(BEEP, OUTPUT);
  pinMode(Latch_Inputs, OUTPUT);
  pinMode(Latch_Outputs, OUTPUT);
  pinMode (HSA, OUTPUT);  // #R200405EAR01 - adds motor mosfet drive
  pinMode (HSB, OUTPUT);  // #R200405EAR01 - adds motor mosfet drive
  pinMode (Red_Led, OUTPUT);  // multipurpose led output
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  // PressureMaxLimit=40;    // PM 15-40 range   
  AssistedPressureThreshold=15; // AP 0-50 range TBD
  // TidalVolumeSet=350;            // TV around 250-800 ml range
  // BPM=12;       // BM 8-30 BPM
  // IE_Ratio=2;      // IE 1-4 1:1 a 1:4


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    // The number 8 was a mult constant used to increase resolution
    Ramping_Speed=(TidalVolumeSet*8)/Ramping_Insp_Time; 

    // Ramping_Speed values ranged from 6 (8 BPM - 200 ml TV) to 125 (30 BPM - 800 ml TV)
    // It seems good enough to build a lookup table
    
    // #R200409EAR03 - Calculates PWM based on Ramping_Speed 
    // =====================================================
    // RS Ramping_Speed values ranged from 6 (8 BPM - 200 ml TV) to 125 (30 BPM - 800 ml TV)

    if (Ramping_Speed > 255) Ramping_Speed=255; // Speed Bump!
    PWM_Ramp=PWM_Table[Ramping_Speed];
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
